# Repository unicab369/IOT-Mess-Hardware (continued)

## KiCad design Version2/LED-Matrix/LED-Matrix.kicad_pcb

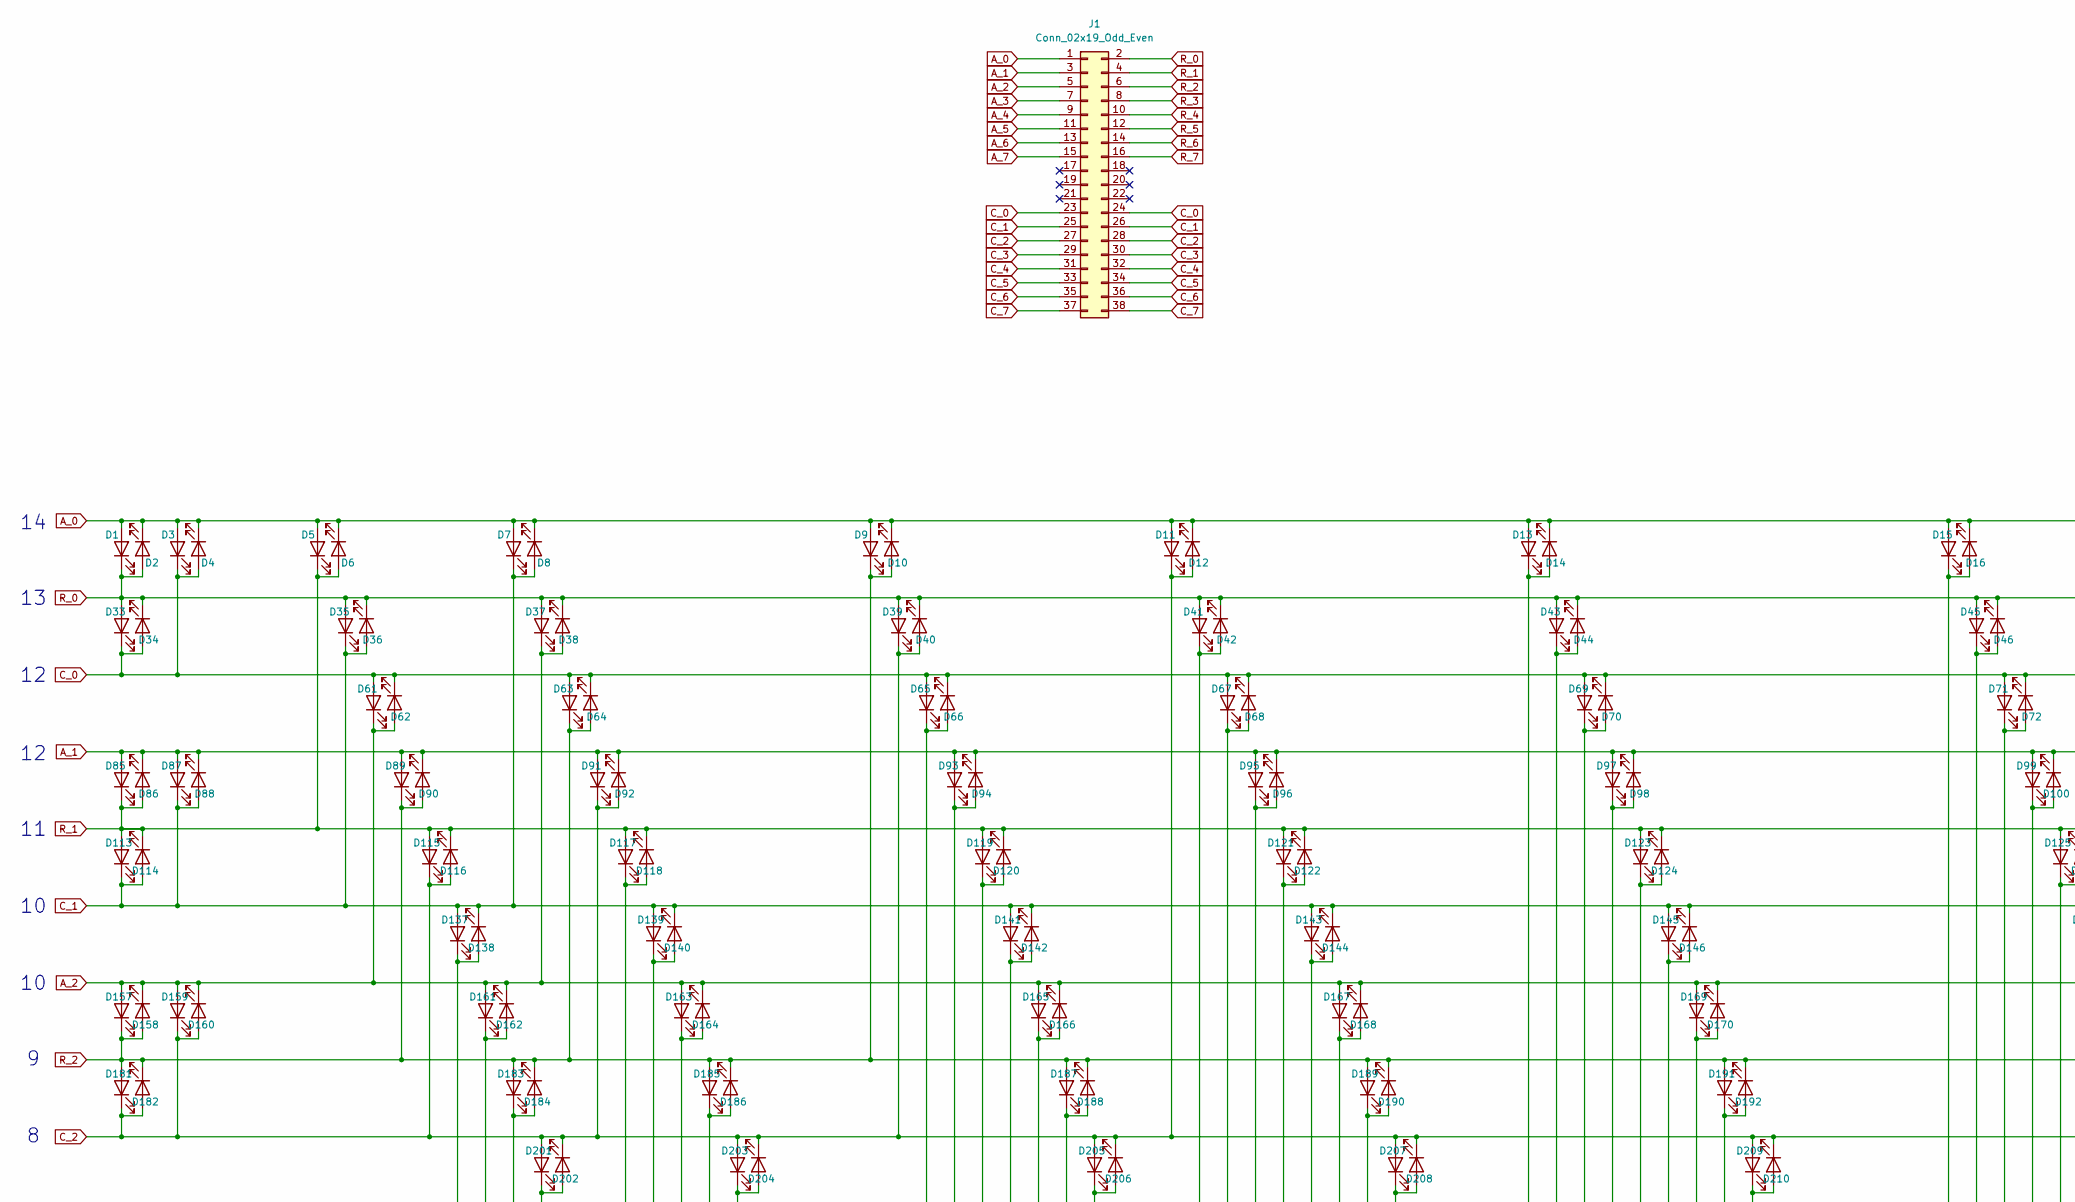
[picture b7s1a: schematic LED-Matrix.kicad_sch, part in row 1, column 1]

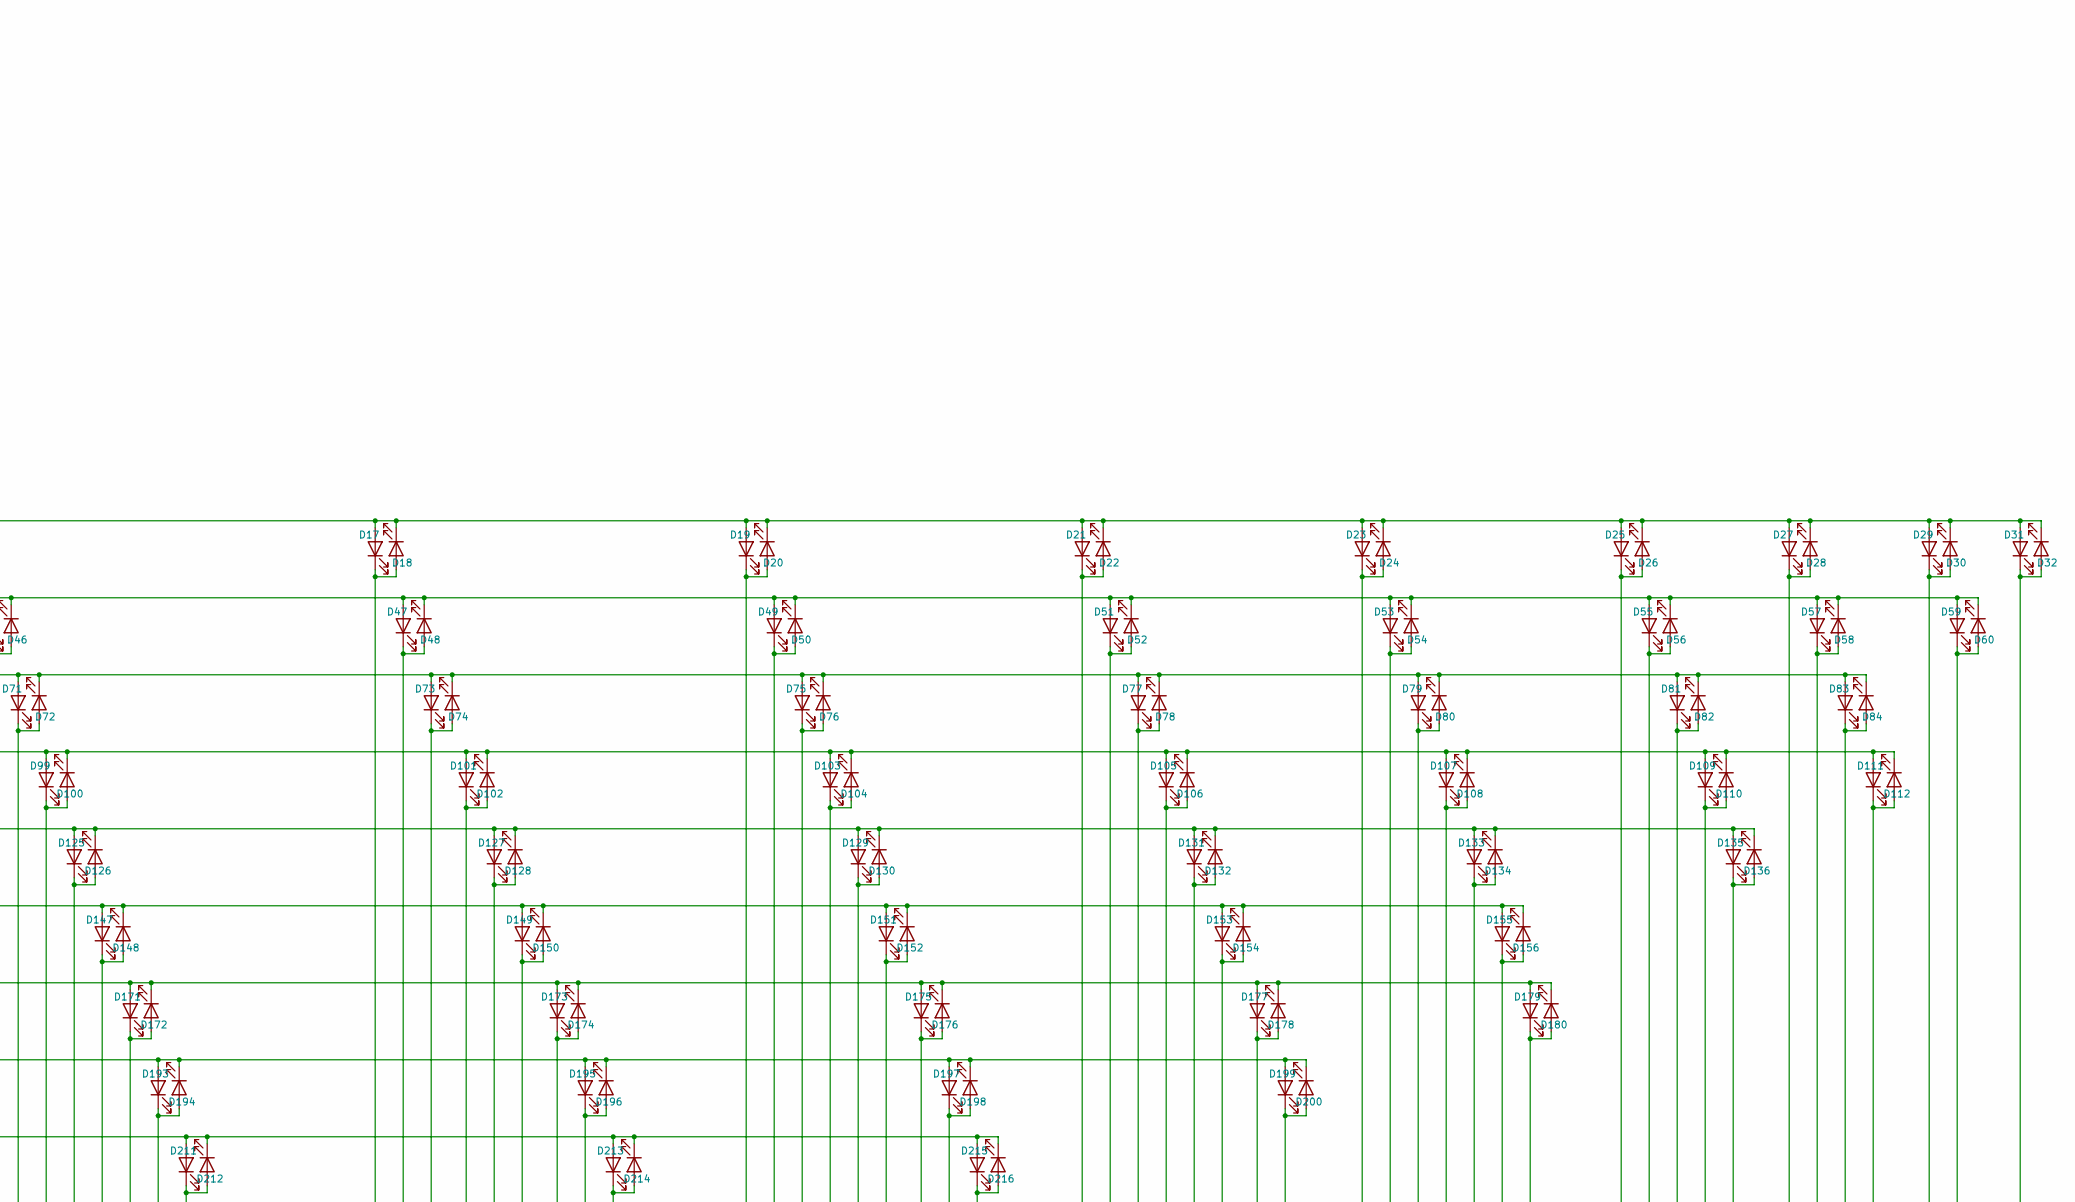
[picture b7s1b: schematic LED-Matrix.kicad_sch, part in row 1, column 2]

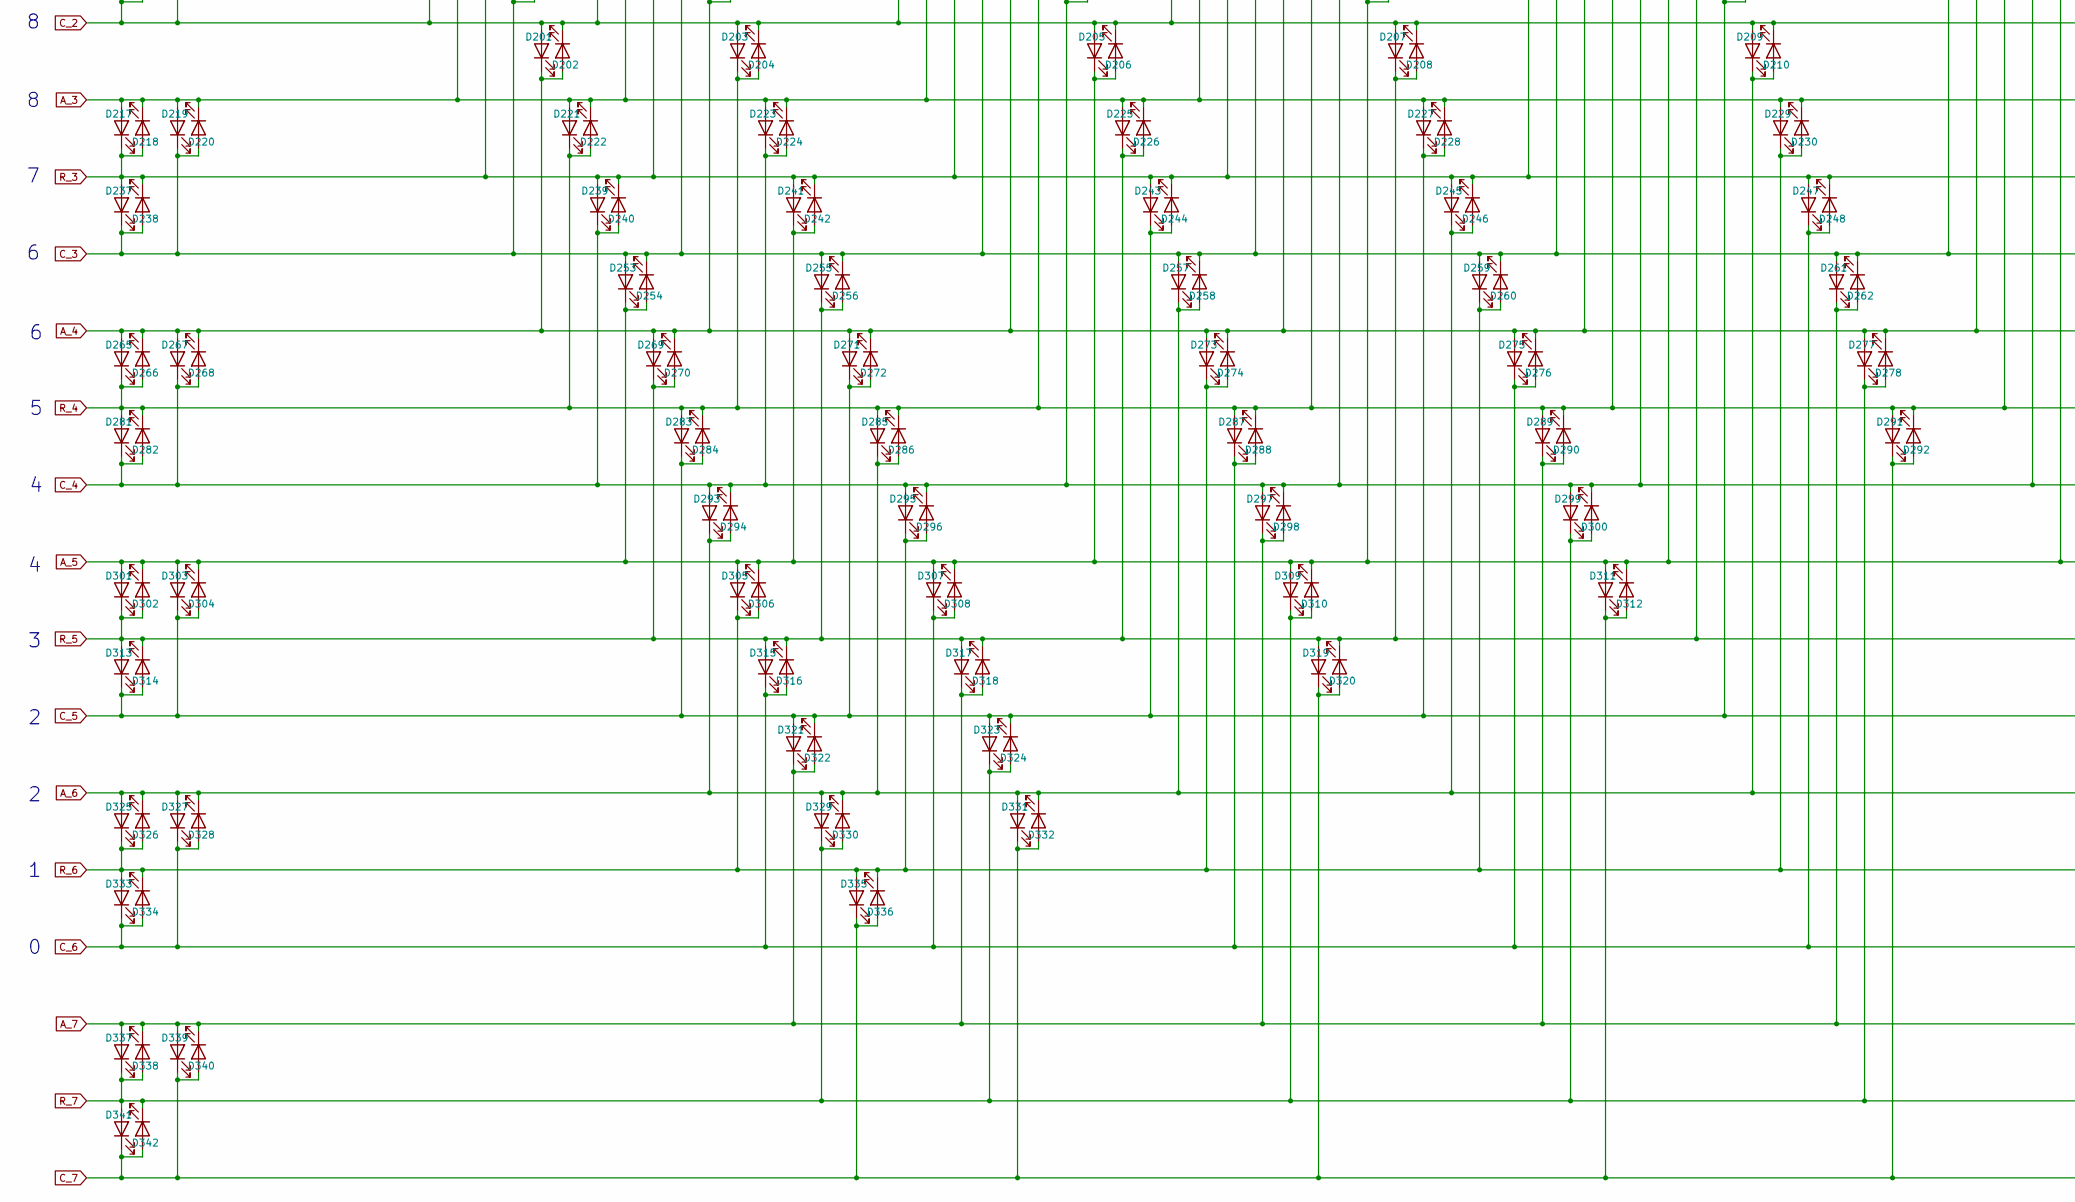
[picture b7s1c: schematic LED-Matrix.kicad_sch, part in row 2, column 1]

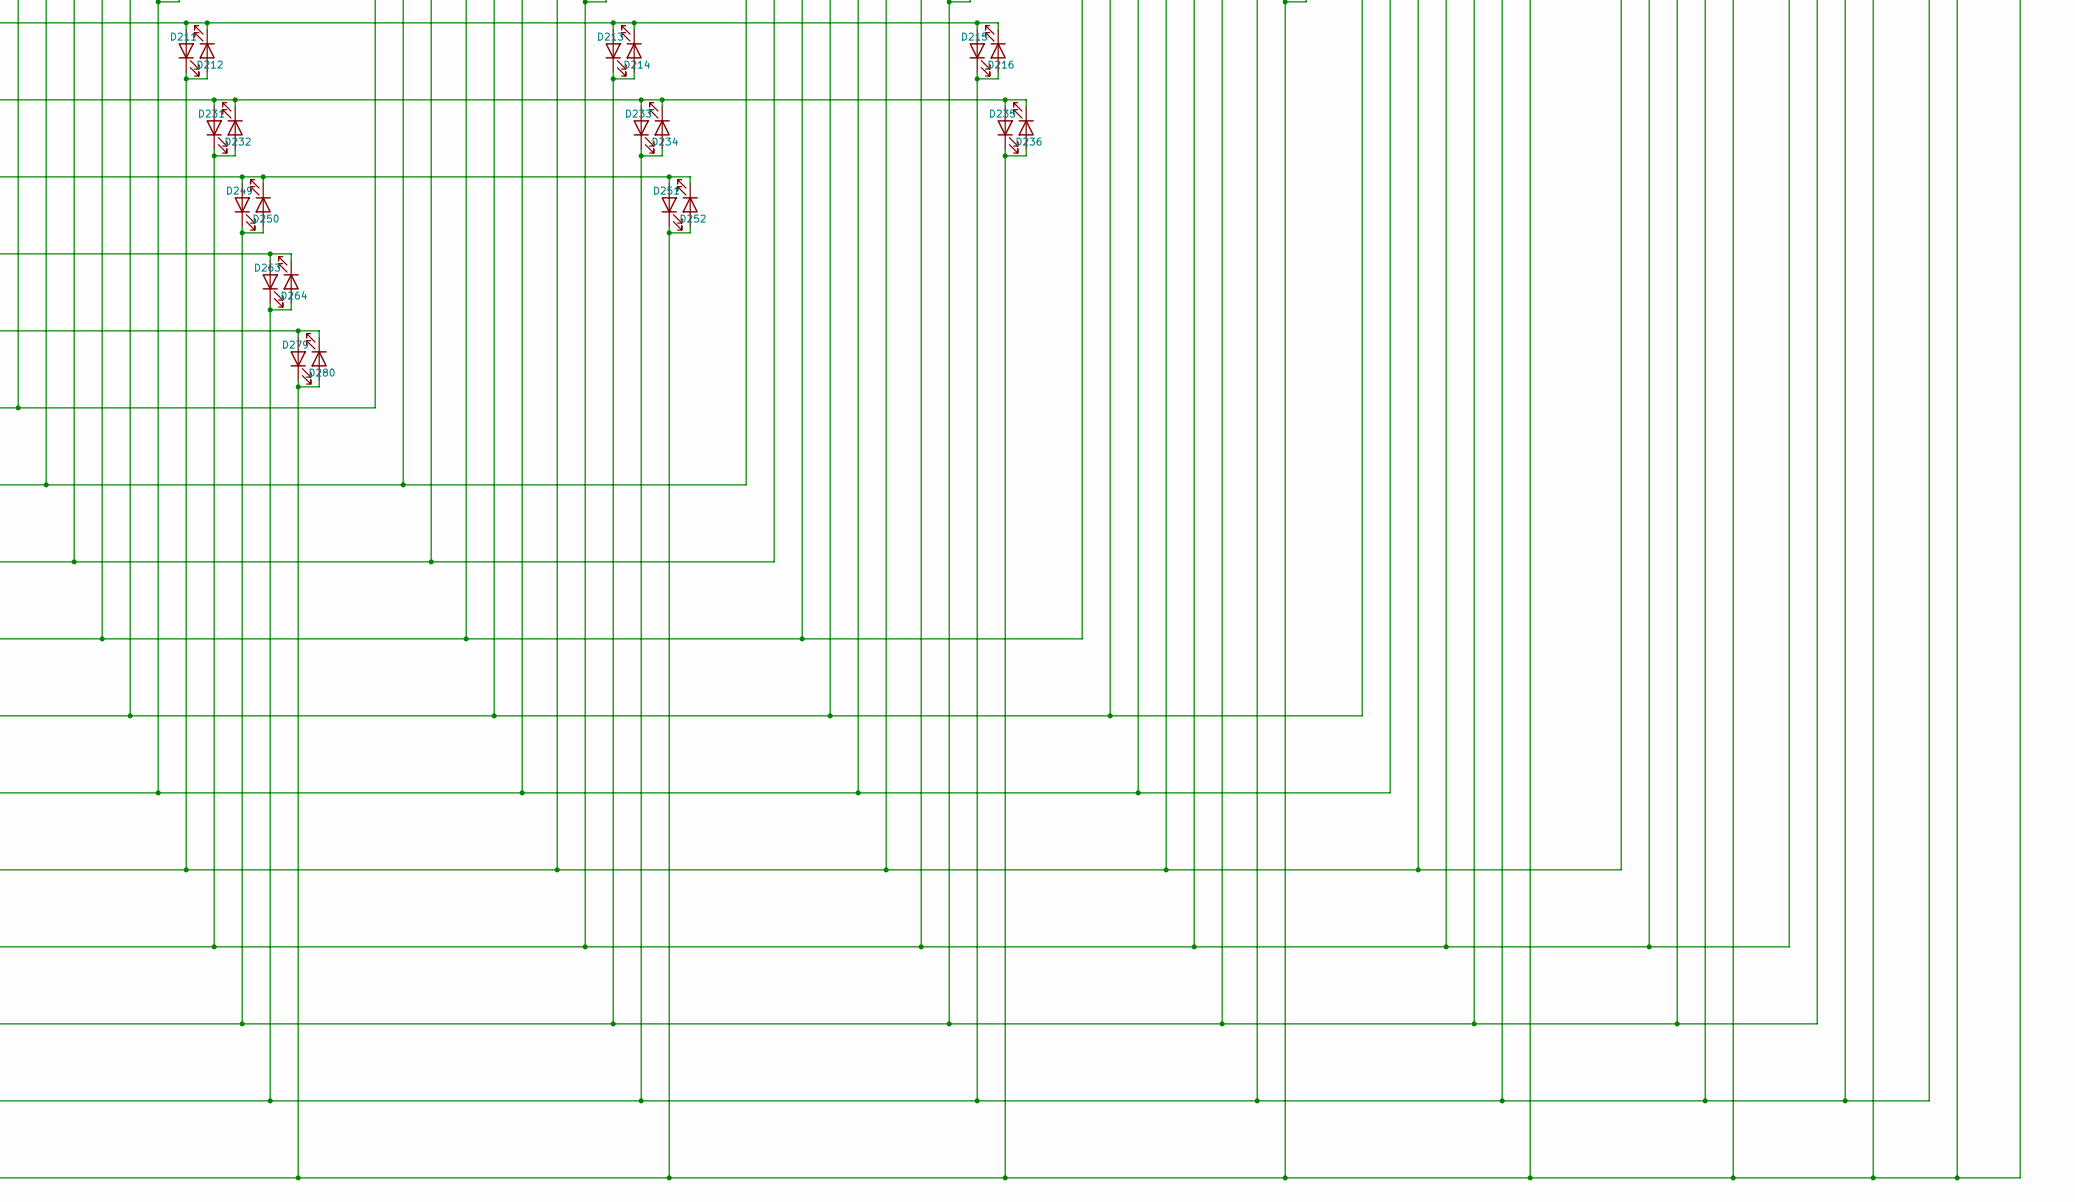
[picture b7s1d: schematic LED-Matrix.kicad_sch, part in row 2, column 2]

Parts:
D1, D2, D3, D4, D5, D6, D7, D8, D9, D10, D11, D12, D13, D14, D15, D16, D17, D18, D19, D20, D21, D22, D23, D24, D25, D26, D27, D28, D29, D30, D31, D32, D33, D34, D35, D36, D37, D38, D39, D40, D41, D42, D43, D44, D45, D46, D47, D48, D49, D50, D51, D52, D53, D54, D55, D56, D57, D58, D59, D60, D61, D62, D63, D64, D65, D66, D67, D68, D69, D70, D71, D72, D73, D74, D75, D76, D77, D78, D79, D80, D81, D82, D83, D84, D85, D86, D87, D88, D89, D90, D91, D92, D93, D94, D95, D96, D97, D98, D99, D100, D101, D102, D103, D104, D105, D106, D107, D108, D109, D110, D111, D112, D113, D114, D115, D116, D117, D118, D119, D120, D121, D122, D123, D124, D125, D126, D127, D128, D129, D130, D131, D132, D133, D134, D135, D136, D137, D138, D139, D140, D141, D142, D143, D144, D145, D146, D147, D148, D149, D150, D151, D152, D153, D154, D155, D156, D157, D158, D159, D160, D161, D162, D163, D164, D165, D166, D167, D168, D169, D170, D171, D172, D173, D174, D175, D176, D177, D178, D179, D180, D181, D182, D183, D184, D185, D186, D187, D188, D189, D190, D191, D192, D193, D194, D195, D196, D197, D198, D199, D200, D201, D202, D203, D204, D205, D206, D207, D208, D209, D210, D211, D212, D213, D214, D215, D216, D217, D218, D219, D220, D221, D222, D223, D224, D225, D226, D227, D228, D229, D230, D231, D232, D233, D234, D235, D236, D237, D238, D239, D240, D241, D242, D243, D244, D245, D246, D247, D248, D249, D250, D251, D252, D253, D254, D255, D256, D257, D258, D259, D260, D261, D262, D263, D264, D265, D266, D267, D268, D269, D270, D271, D272, D273, D274, D275, D276, D277, D278, D279, D280, D281, D282, D283, D284, D285, D286, D287, D288, D289, D290, D291, D292, D293, D294, D295, D296, D297, D298, D299, D300, D301, D302, D303, D304, D305, D306, D307, D308, D309, D310, D311, D312, D313, D314, D315, D316, D317, D318, D319, D320, D321, D322, D323, D324, D325, D326, D327, D328, D329, D330, D331, D332, D333, D334, D335, D336, D337, D338, D339, D340, D341, D342: LED; LED_0603_1608Metric_Pad1.05x0.95mm_HandSolder
J1: Conn_02x19_Odd_Even; PinHeader_2x19_P2.54mm_Vertical

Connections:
A_0: D1.2 (A), D2.1 (K), D3.2 (A), D4.1 (K), D5.2 (A), D6.1 (K), D7.2 (A), D8.1 (K), D9.2 (A), D10.1 (K), D11.2 (A), D12.1 (K), D13.2 (A), D14.1 (K), D15.2 (A), D16.1 (K), D17.2 (A), D18.1 (K), D19.2 (A), D20.1 (K), D21.2 (A), D22.1 (K), D23.2 (A), D24.1 (K), D25.2 (A), D26.1 (K), D27.2 (A), D28.1 (K), D29.2 (A), D30.1 (K), D31.2 (A), D32.1 (K), J1.1
A_1: D85.2 (A), D86.1 (K), D87.2 (A), D88.1 (K), D89.2 (A), D90.1 (K), D91.2 (A), D92.1 (K), D93.2 (A), D94.1 (K), D95.2 (A), D96.1 (K), D97.2 (A), D98.1 (K), D99.2 (A), D100.1 (K), D101.2 (A), D102.1 (K), D103.2 (A), D104.1 (K), D105.2 (A), D106.1 (K), D107.2 (A), D108.1 (K), D109.2 (A), D110.1 (K), D111.2 (A), D112.1 (K), J1.3
A_2: D37.1 (K), D38.2 (A), D61.1 (K), D62.2 (A), D157.2 (A), D158.1 (K), D159.2 (A), D160.1 (K), D161.2 (A), D162.1 (K), D163.2 (A), D164.1 (K), D165.2 (A), D166.1 (K), D167.2 (A), D168.1 (K), D169.2 (A), D170.1 (K), D171.2 (A), D172.1 (K), D173.2 (A), D174.1 (K), D175.2 (A), D176.1 (K), D177.2 (A), D178.1 (K), D179.2 (A), D180.1 (K), J1.5
A_3: D41.1 (K), D42.2 (A), D65.1 (K), D66.2 (A), D117.1 (K), D118.2 (A), D137.1 (K), D138.2 (A), D217.2 (A), D218.1 (K), D219.2 (A), D220.1 (K), D221.2 (A), D222.1 (K), D223.2 (A), D224.1 (K), D225.2 (A), D226.1 (K), D227.2 (A), D228.1 (K), D229.2 (A), D230.1 (K), D231.2 (A), D232.1 (K), D233.2 (A), D234.1 (K), D235.2 (A), D236.1 (K), J1.7
A_4: D45.1 (K), D46.2 (A), D69.1 (K), D70.2 (A), D121.1 (K), D122.2 (A), D141.1 (K), D142.2 (A), D185.1 (K), D186.2 (A), D201.1 (K), D202.2 (A), D265.2 (A), D266.1 (K), D267.2 (A), D268.1 (K), D269.2 (A), D270.1 (K), D271.2 (A), D272.1 (K), D273.2 (A), D274.1 (K), D275.2 (A), D276.1 (K), D277.2 (A), D278.1 (K), D279.2 (A), D280.1 (K), J1.9
A_5: D49.1 (K), D50.2 (A), D73.1 (K), D74.2 (A), D125.1 (K), D126.2 (A), D145.1 (K), D146.2 (A), D189.1 (K), D190.2 (A), D205.1 (K), D206.2 (A), D241.1 (K), D242.2 (A), D253.1 (K), D254.2 (A), D301.2 (A), D302.1 (K), D303.2 (A), D304.1 (K), D305.2 (A), D306.1 (K), D307.2 (A), D308.1 (K), D309.2 (A), D310.1 (K), D311.2 (A), D312.1 (K), J1.11
A_6: D53.1 (K), D54.2 (A), D77.1 (K), D78.2 (A), D129.1 (K), D130.2 (A), D149.1 (K), D150.2 (A), D193.1 (K), D194.2 (A), D209.1 (K), D210.2 (A), D245.1 (K), D246.2 (A), D257.1 (K), D258.2 (A), D285.1 (K), D286.2 (A), D293.1 (K), D294.2 (A), D325.2 (A), D326.1 (K), D327.2 (A), D328.1 (K), D329.2 (A), D330.1 (K), D331.2 (A), D332.1 (K), J1.13
A_7: D57.1 (K), D58.2 (A), D81.1 (K), D82.2 (A), D133.1 (K), D134.2 (A), D153.1 (K), D154.2 (A), D197.1 (K), D198.2 (A), D213.1 (K), D214.2 (A), D249.1 (K), D250.2 (A), D261.1 (K), D262.2 (A), D289.1 (K), D290.2 (A), D297.1 (K), D298.2 (A), D317.1 (K), D318.2 (A), D321.1 (K), D322.2 (A), D337.2 (A), D338.1 (K), D339.2 (A), D340.1 (K), J1.15
C_0: D3.1 (K), D4.2 (A), D33.1 (K), D34.2 (A), D61.2 (A), D62.1 (K), D63.2 (A), D64.1 (K), D65.2 (A), D66.1 (K), D67.2 (A), D68.1 (K), D69.2 (A), D70.1 (K), D71.2 (A), D72.1 (K), D73.2 (A), D74.1 (K), D75.2 (A), D76.1 (K), D77.2 (A), D78.1 (K), D79.2 (A), D80.1 (K), D81.2 (A), D82.1 (K), D83.2 (A), D84.1 (K), J1.23, J1.24
C_1: D7.1 (K), D8.2 (A), D35.1 (K), D36.2 (A), D87.1 (K), D88.2 (A), D113.1 (K), D114.2 (A), D137.2 (A), D138.1 (K), D139.2 (A), D140.1 (K), D141.2 (A), D142.1 (K), D143.2 (A), D144.1 (K), D145.2 (A), D146.1 (K), D147.2 (A), D148.1 (K), D149.2 (A), D150.1 (K), D151.2 (A), D152.1 (K), D153.2 (A), D154.1 (K), D155.2 (A), D156.1 (K), J1.25, J1.26
C_2: D11.1 (K), D12.2 (A), D39.1 (K), D40.2 (A), D91.1 (K), D92.2 (A), D115.1 (K), D116.2 (A), D159.1 (K), D160.2 (A), D181.1 (K), D182.2 (A), D201.2 (A), D202.1 (K), D203.2 (A), D204.1 (K), D205.2 (A), D206.1 (K), D207.2 (A), D208.1 (K), D209.2 (A), D210.1 (K), D211.2 (A), D212.1 (K), D213.2 (A), D214.1 (K), D215.2 (A), D216.1 (K), J1.27, J1.28
C_3: D15.1 (K), D16.2 (A), D43.1 (K), D44.2 (A), D95.1 (K), D96.2 (A), D119.1 (K), D120.2 (A), D163.1 (K), D164.2 (A), D183.1 (K), D184.2 (A), D219.1 (K), D220.2 (A), D237.1 (K), D238.2 (A), D253.2 (A), D254.1 (K), D255.2 (A), D256.1 (K), D257.2 (A), D258.1 (K), D259.2 (A), D260.1 (K), D261.2 (A), D262.1 (K), D263.2 (A), D264.1 (K), J1.29, J1.30
C_4: D19.1 (K), D20.2 (A), D47.1 (K), D48.2 (A), D99.1 (K), D100.2 (A), D123.1 (K), D124.2 (A), D167.1 (K), D168.2 (A), D187.1 (K), D188.2 (A), D223.1 (K), D224.2 (A), D239.1 (K), D240.2 (A), D267.1 (K), D268.2 (A), D281.1 (K), D282.2 (A), D293.2 (A), D294.1 (K), D295.2 (A), D296.1 (K), D297.2 (A), D298.1 (K), D299.2 (A), D300.1 (K), J1.31, J1.32
C_5: D23.1 (K), D24.2 (A), D51.1 (K), D52.2 (A), D103.1 (K), D104.2 (A), D127.1 (K), D128.2 (A), D171.1 (K), D172.2 (A), D191.1 (K), D192.2 (A), D227.1 (K), D228.2 (A), D243.1 (K), D244.2 (A), D271.1 (K), D272.2 (A), D283.1 (K), D284.2 (A), D303.1 (K), D304.2 (A), D313.1 (K), D314.2 (A), D321.2 (A), D322.1 (K), D323.2 (A), D324.1 (K), J1.33, J1.34
C_6: D27.1 (K), D28.2 (A), D55.1 (K), D56.2 (A), D107.1 (K), D108.2 (A), D131.1 (K), D132.2 (A), D175.1 (K), D176.2 (A), D195.1 (K), D196.2 (A), D231.1 (K), D232.2 (A), D247.1 (K), D248.2 (A), D275.1 (K), D276.2 (A), D287.1 (K), D288.2 (A), D307.1 (K), D308.2 (A), D315.1 (K), D316.2 (A), D327.1 (K), D328.2 (A), D333.1 (K), D334.2 (A), J1.35, J1.36
C_7: D31.1 (K), D32.2 (A), D59.1 (K), D60.2 (A), D111.1 (K), D112.2 (A), D135.1 (K), D136.2 (A), D179.1 (K), D180.2 (A), D199.1 (K), D200.2 (A), D235.1 (K), D236.2 (A), D251.1 (K), D252.2 (A), D279.1 (K), D280.2 (A), D291.1 (K), D292.2 (A), D311.1 (K), D312.2 (A), D319.1 (K), D320.2 (A), D331.1 (K), D332.2 (A), D335.1 (K), D336.2 (A), D339.1 (K), D340.2 (A), D341.1 (K), D342.2 (A), J1.37, J1.38
R_0: D1.1 (K), D2.2 (A), D33.2 (A), D34.1 (K), D35.2 (A), D36.1 (K), D37.2 (A), D38.1 (K), D39.2 (A), D40.1 (K), D41.2 (A), D42.1 (K), D43.2 (A), D44.1 (K), D45.2 (A), D46.1 (K), D47.2 (A), D48.1 (K), D49.2 (A), D50.1 (K), D51.2 (A), D52.1 (K), D53.2 (A), D54.1 (K), D55.2 (A), D56.1 (K), D57.2 (A), D58.1 (K), D59.2 (A), D60.1 (K), J1.2
R_1: D5.1 (K), D6.2 (A), D85.1 (K), D86.2 (A), D113.2 (A), D114.1 (K), D115.2 (A), D116.1 (K), D117.2 (A), D118.1 (K), D119.2 (A), D120.1 (K), D121.2 (A), D122.1 (K), D123.2 (A), D124.1 (K), D125.2 (A), D126.1 (K), D127.2 (A), D128.1 (K), D129.2 (A), D130.1 (K), D131.2 (A), D132.1 (K), D133.2 (A), D134.1 (K), D135.2 (A), D136.1 (K), J1.4
R_2: D9.1 (K), D10.2 (A), D63.1 (K), D64.2 (A), D89.1 (K), D90.2 (A), D157.1 (K), D158.2 (A), D181.2 (A), D182.1 (K), D183.2 (A), D184.1 (K), D185.2 (A), D186.1 (K), D187.2 (A), D188.1 (K), D189.2 (A), D190.1 (K), D191.2 (A), D192.1 (K), D193.2 (A), D194.1 (K), D195.2 (A), D196.1 (K), D197.2 (A), D198.1 (K), D199.2 (A), D200.1 (K), J1.6
R_3: D13.1 (K), D14.2 (A), D67.1 (K), D68.2 (A), D93.1 (K), D94.2 (A), D139.1 (K), D140.2 (A), D161.1 (K), D162.2 (A), D217.1 (K), D218.2 (A), D237.2 (A), D238.1 (K), D239.2 (A), D240.1 (K), D241.2 (A), D242.1 (K), D243.2 (A), D244.1 (K), D245.2 (A), D246.1 (K), D247.2 (A), D248.1 (K), D249.2 (A), D250.1 (K), D251.2 (A), D252.1 (K), J1.8
R_4: D17.1 (K), D18.2 (A), D71.1 (K), D72.2 (A), D97.1 (K), D98.2 (A), D143.1 (K), D144.2 (A), D165.1 (K), D166.2 (A), D203.1 (K), D204.2 (A), D221.1 (K), D222.2 (A), D265.1 (K), D266.2 (A), D281.2 (A), D282.1 (K), D283.2 (A), D284.1 (K), D285.2 (A), D286.1 (K), D287.2 (A), D288.1 (K), D289.2 (A), D290.1 (K), D291.2 (A), D292.1 (K), J1.10
R_5: D21.1 (K), D22.2 (A), D75.1 (K), D76.2 (A), D101.1 (K), D102.2 (A), D147.1 (K), D148.2 (A), D169.1 (K), D170.2 (A), D207.1 (K), D208.2 (A), D225.1 (K), D226.2 (A), D255.1 (K), D256.2 (A), D269.1 (K), D270.2 (A), D301.1 (K), D302.2 (A), D313.2 (A), D314.1 (K), D315.2 (A), D316.1 (K), D317.2 (A), D318.1 (K), D319.2 (A), D320.1 (K), J1.12
R_6: D25.1 (K), D26.2 (A), D79.1 (K), D80.2 (A), D105.1 (K), D106.2 (A), D151.1 (K), D152.2 (A), D173.1 (K), D174.2 (A), D211.1 (K), D212.2 (A), D229.1 (K), D230.2 (A), D259.1 (K), D260.2 (A), D273.1 (K), D274.2 (A), D295.1 (K), D296.2 (A), D305.1 (K), D306.2 (A), D325.1 (K), D326.2 (A), D333.2 (A), D334.1 (K), D335.2 (A), D336.1 (K), J1.14
R_7: D29.1 (K), D30.2 (A), D83.1 (K), D84.2 (A), D109.1 (K), D110.2 (A), D155.1 (K), D156.2 (A), D177.1 (K), D178.2 (A), D215.1 (K), D216.2 (A), D233.1 (K), D234.2 (A), D263.1 (K), D264.2 (A), D277.1 (K), D278.2 (A), D299.1 (K), D300.2 (A), D309.1 (K), D310.2 (A), D323.1 (K), D324.2 (A), D329.1 (K), D330.2 (A), D337.1 (K), D338.2 (A), D341.2 (A), D342.1 (K), J1.16

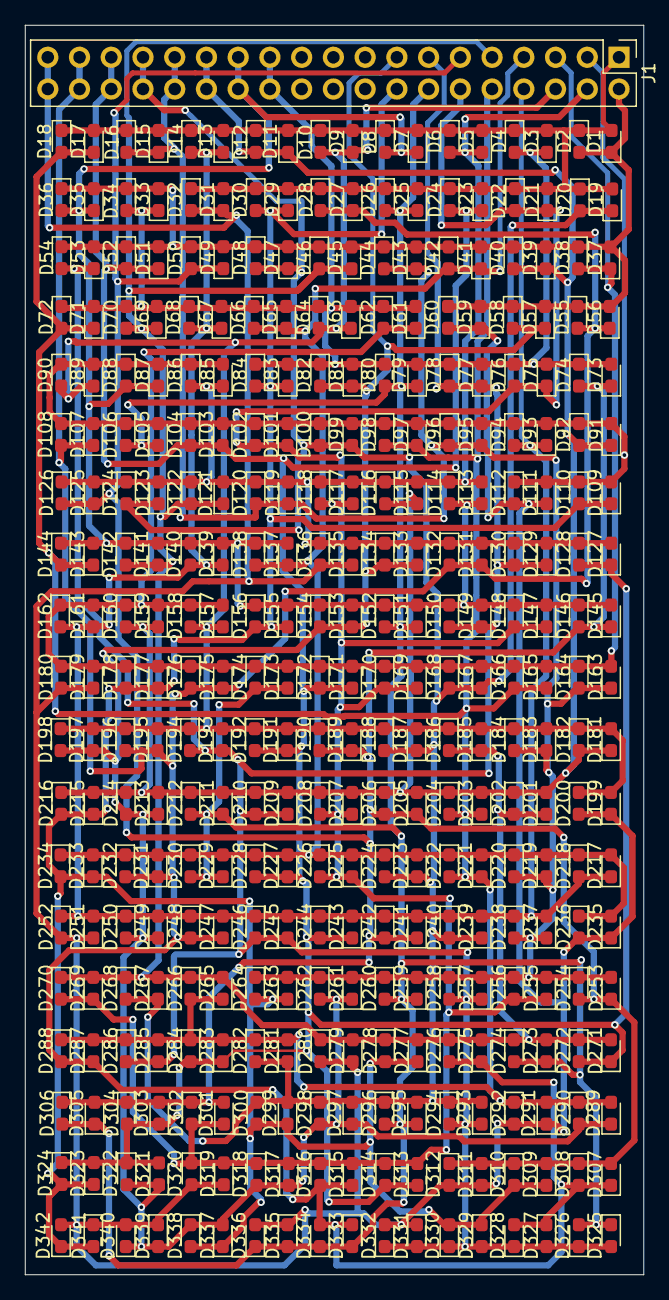
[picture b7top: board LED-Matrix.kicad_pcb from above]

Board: 2 copper layers, 49.5 x 100.0 mm, 343 parts (0 on the bottom side), 24 nets.
